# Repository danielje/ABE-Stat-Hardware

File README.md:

# ABE-Stat-Hardware
ABE-Stat Hardware Design / Assembly Files
For Android source code for wireless interface for device, go to https://github.com/danielje/ABE-Stat
For firmware source code (Arduino IDE) go to https://github.com/danielje/ABE-Stat-Arduino

Comprehensive documentation for the project is available in the open-source publication here: http://jes.ecsdl.org/content/166/9/B3056.short This set of files is referred to as "Files S1" in the manuscript above.

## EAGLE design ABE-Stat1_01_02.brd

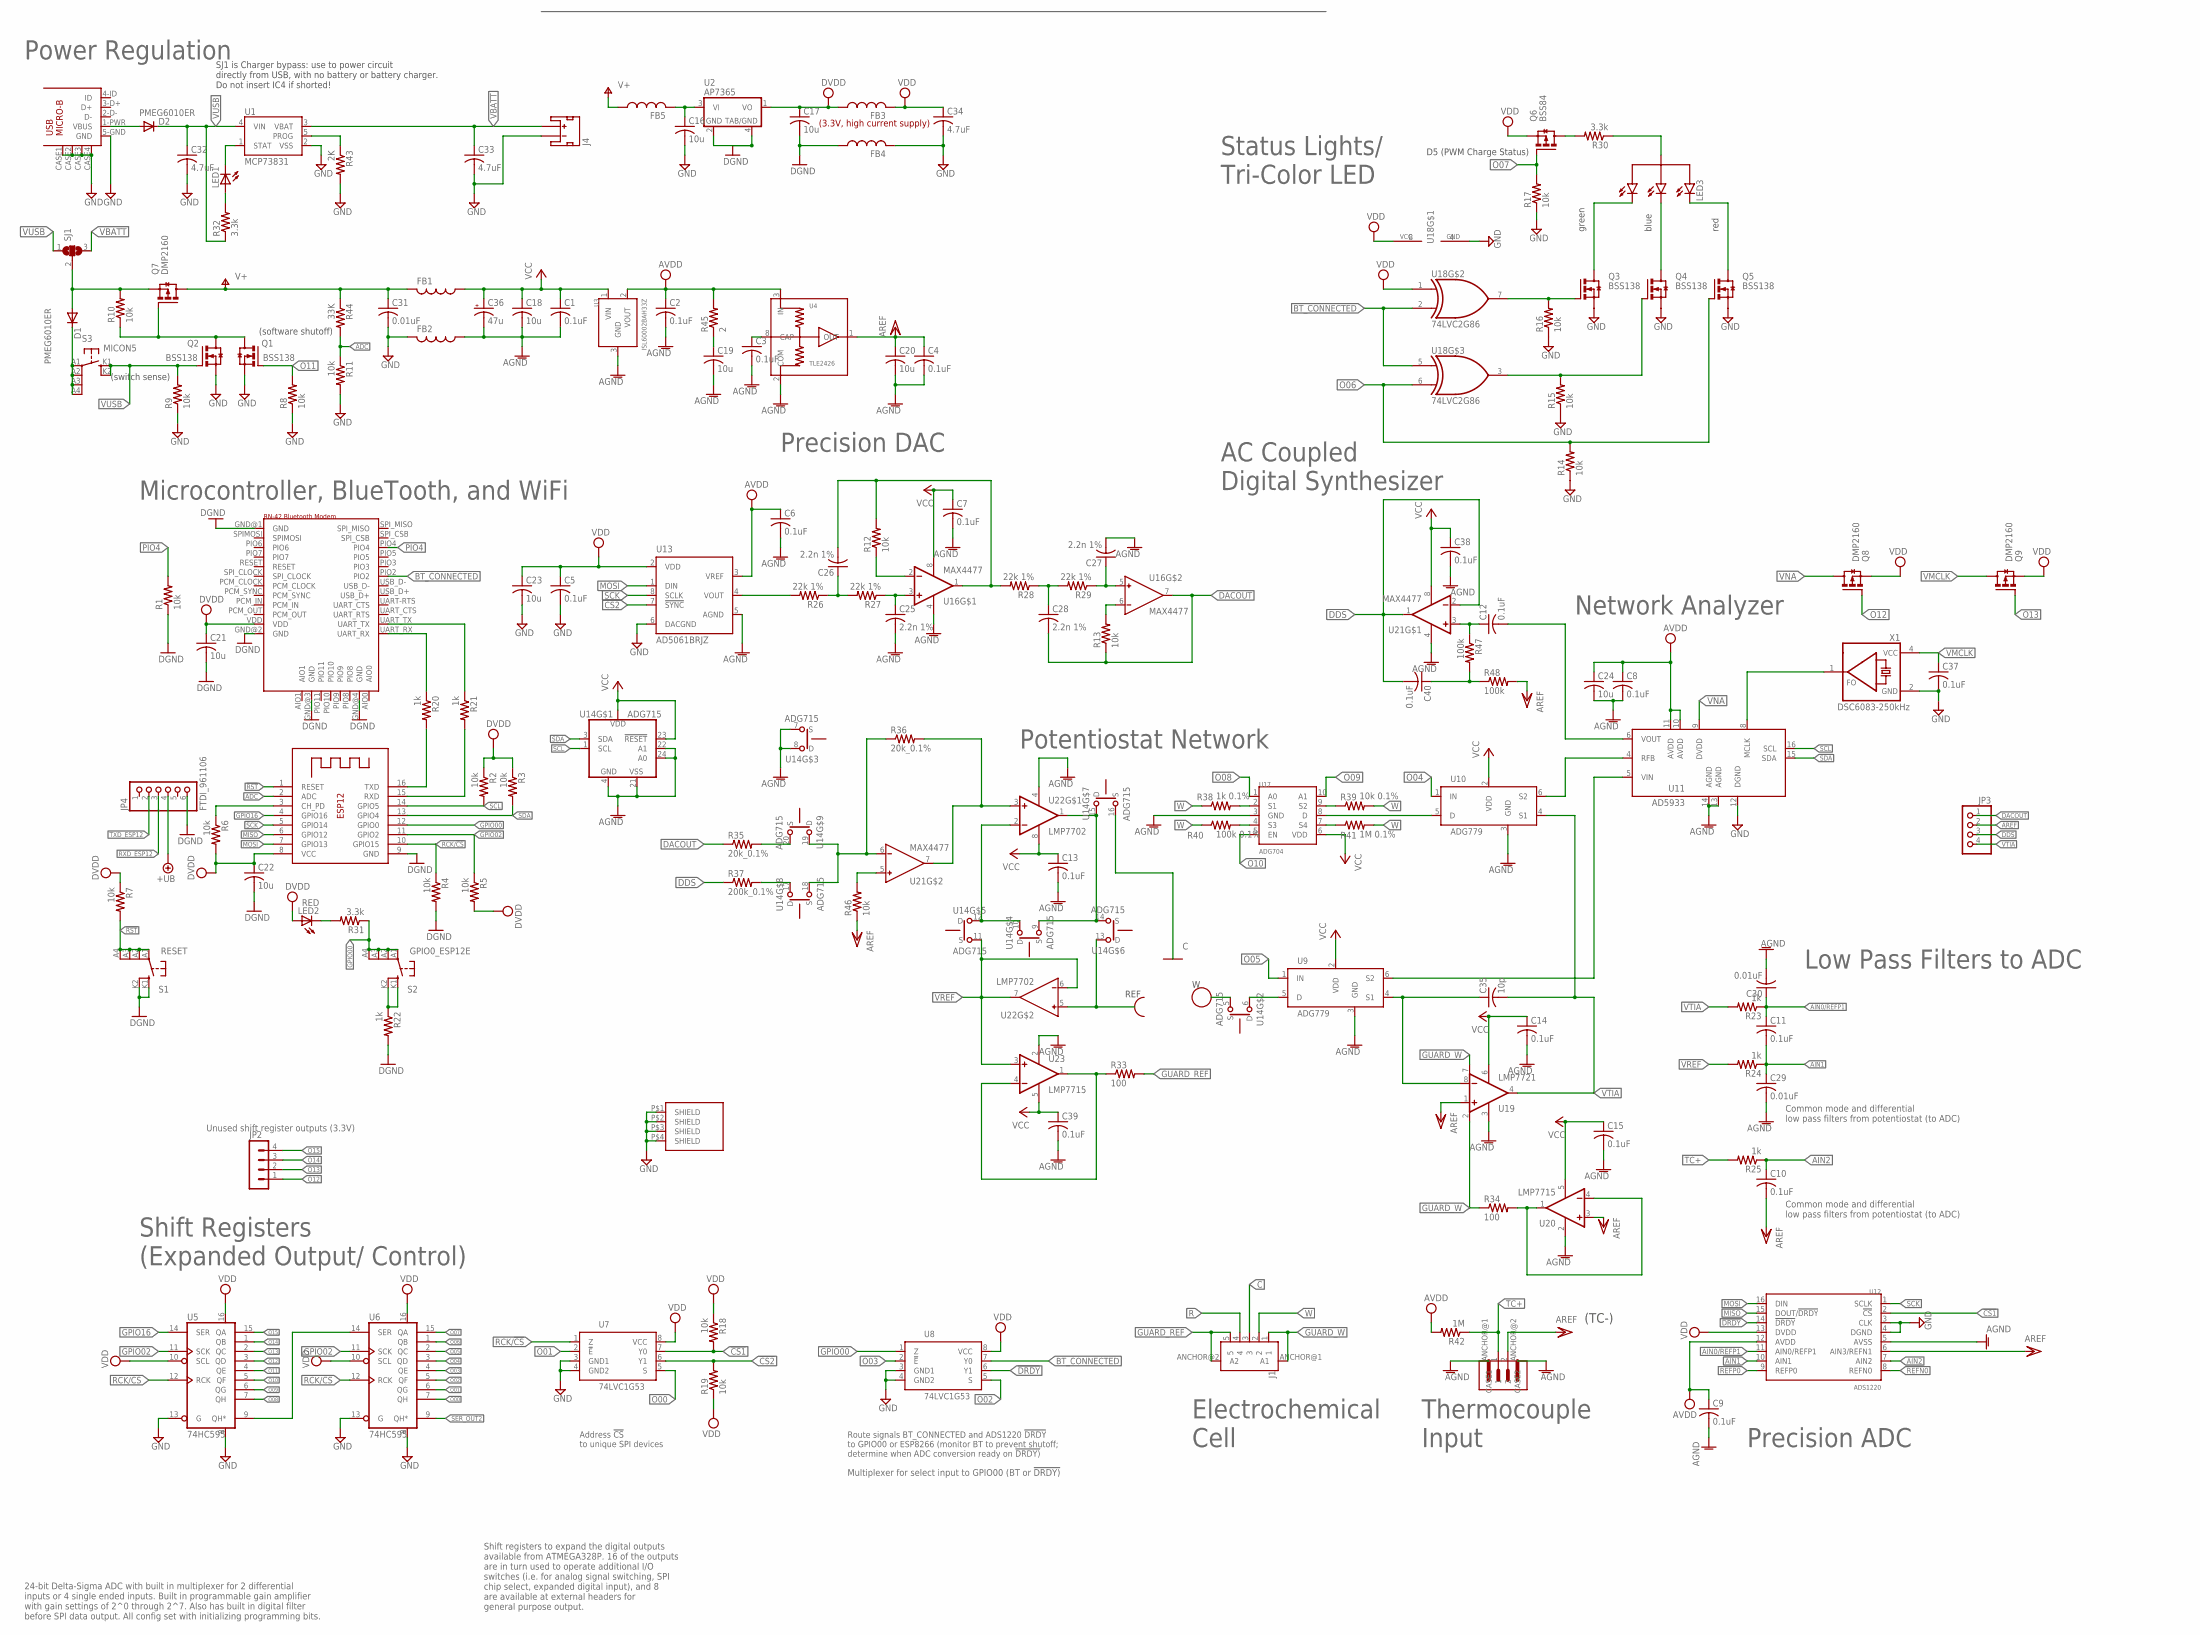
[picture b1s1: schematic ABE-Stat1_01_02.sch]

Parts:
A1: ESP-12E; ESP-12
A2: RN-42_BLUETOOTH; RN-42
C1, C2, C3, C4, C5, C6, C7, C8, C9, C10, C11, C12, C13, C14, C15, C37, C38, C39, C40: 0.1uF; C0805
C16, C17, C18, C19, C20, C21, C22, C23, C24: 10u; C0805
C25, C26, C27, C28: 2.2n 1%; C0805
C29, C30, C31: 0.01uF; C0805
C32, C33, C34: 4.7uF; C0805
C35: 10p; C0805
C36: 47u; D/7343-31W
D1, D2: PMEG6010ER; DIODE_SOD123
FB1, FB2, FB3, FB4, FB5: FERRITE_BEAD_5A_0805; R0805
J1: 5-PIN-VERTICAL-PHOENIX_2.5MM-SMD; 5-PIN-VERT_PHOENIX_SMD
J2: 1A_JENKINS_2013_2PIN_SMD_PHOENIX_CONTACTVERTICAL; 2-PIN-VERT_PHOENIX_SMD
J3: USB-MICRO-B; USB_MICRO_B_WURTH_629105136821
J4: JST_2MM_MALE; JST-2-SMD
JP2: MA04-1
JP3: PINHD-1X4; 1X04
JP4: FTDI_961106; 6_PIN_0.1IN_STRAIGHT_HEADER
LED1: LEDCHIPLED_1206; CHIPLED_1206
LED2: RED; LED-1206
LED3: LED_RBG_COM_ANODE; LED_RGB_WURTH_150141M173100
Q1, Q2, Q3, Q4, Q5: BSS138; SOT-23
Q6: BSS84; SOT-23-3
Q7, Q8, Q9: DMP2160; SOT-23-3
R1, R2, R3, R4, R5, R6, R7, R8, R9, R10, R11, R12, R13, R14, R15, R16, R17, R18, R19, R46: 10k; R0805
R20, R21, R22, R23, R24, R25: 1k; R0805
R26, R27, R28, R29: 22k 1%; R0805
R30, R31, R32: 3.3k; R0805
R33, R34: 100; R0805
R35, R36: 20k_0.1%; R0805
R37: 200k_0.1%; R0805
R38: 1k 0.1%; R0805
R39: 10k 0.1%; R0805
R40: 100k 0.1%; R0805
R41: 1M 0.1%; R0805
R42: 1M; R0805
R43: 2K; R0805
R44: 33K; R0805
R45: 2; R2512
R47, R48: 100k; R0805
S1: RESET; RAFI-MICON5_SWITCH
S2: GPIO0_ESP12E; RAFI-MICON5_SWITCH
S3: MICON5; RAFI-MICON5_SWITCH
SH1: SMARTDART_SHIELD; SMARTDART-SHIELD
SJ1: SJ2W; SJ_2
U1: MCP73831; SOT23-5
U2: AP7365; SOT-223
U3: ISL60002BAH33Z; SOT-23-3
U4: TLE2426; SOIC-8
U5, U6: 74HC595; TSSOP16
U7, U8: 74LVC1G53; VSSOP8
U9, U10: ADG779; SC70-6
U11: AD5933; SSOP-16
U12: ADS1220; TSSOP16
U13: AD5061BRJZ; SOT-23-8
U14: ADG715; TSSOP24
U16, U21: MAX4477; UMAX8
U17: ADG704; MSOP10
U18: 74LVC2G86; US-8
U19: LMP7721; SOIC-8
U20, U23: LMP7715; SOT23-5
U22: LMP7702; MSOP8
X1: DSC6083-250kHz; DSC60XX_OSCILLATOR_3.2X2.5MM

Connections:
!CS1: R18.2, U7.7 (Y0), U12.2 (!CS)
!CS2: R19.2, U7.6 (Y1), U13.7 (!SYNC)
!DRDY: U8.6 (Y1), U12.14 (!DRDY)
!RST: A1.1 (RESET), R7.2, S1.A1, S1.A2 (P1), S1.A3 (P2), S1.A4 (P3)
+UB: JP4.4
AD5933_VIN: U9.6 (S2), U11.5 (VIN)
ADC: A1.2 (ADC), R11.1, R44.2
AGND: C1.2, C2.2, C3.2, C4.2, C6.2, C7.2, C8.2, C9.2, C13.2, C14.2, C15.2, C18.2, C19.2, C20.2, C24.2, C25.2, C27.2, C29.2, C30.2, C36.-, C38.2, C39.2, FB2.1, J2.ANCHOR@1 (CASE1), J2.ANCHOR@2 (CASE2), U3.3 (GND), U4.2 (COM), U9.3 (GND), U10.3 (GND), U11.13 (AGND), U11.14 (AGND), U12.5 (AVSS), U13.5 (AGND), U14.4 (GND), U14.7 (S), U14.8 (D), U14.21 (VSS), U14.22 (A1), U14.24 (A0), U16.4 (V-), U17.3 (GND), U19.3 (V-), U20.2 (V-), U21.4 (V-), U22.4 (V-), U23.2 (V-)
AIN0/REFP1: C11.1, C30.1, R23.1, U12.11 (AIN0/REFP1)
AIN1: C11.2, C29.1, R24.1, U12.10 (AIN1)
AIN2: C10.1, R25.1, U12.7 (AIN2)
AREF: C4.1, C10.2, C20.1, J2.2, JP3.2, R46.1, R48.2, U4.1 (OUT), U12.6 (AIN3/REFN1), U19.1 (+IN), U20.3 (+IN)
AVDD: C2.1, C6.1, C8.1, C9.1, C24.1, R42.2, R45.2, U3.2 (VOUT), U4.3 (IN), U11.10 (AVDD), U11.11 (AVDD), U12.12 (AVDD), U13.3 (VREF)
BT_CONNECTED: A2.PIO2, U8.7 (Y0), U18.2 (I1), U18.5 (I0)
C: J1.3, U14.16 (S)
DACOUT: C28.2, JP3.1, R13.1, R35.1, U16.7 (OUT)
DDS: C40.2, JP3.3, R37.1, U21.1 (OUT), U21.2 (-IN)
DGND: A1.9 (GND), A2.GND@1 (GND), A2.GND@2 (GND), A2.GND@3 (GND), A2.GND@4 (GND), C17.2, C21.2, C22.2, FB4.1, JP4.6, R1.1, R4.2, R22.2, S1.K1 (S), S1.K2 (S1), U2.2 (GND), U2.4 (GND1)
DVDD: A1.8 (VCC), A2.VDD, C17.1, C21.1, C22.1, FB3.1, LED2.A, R2.1, R3.1, R5.2, R6.2, R7.1, U2.1 (VO)
GND: C5.2, C16.2, C23.2, C31.2, C32.2, C33.2, C34.2, C37.2, FB2.2, FB4.2, J3.5-GND (GND), J3.CASE1 (CASE), J3.CASE2 (CASE), J3.CASE3 (CASE), J3.CASE4 (CASE), J4.1 (-), Q1.2-S (S), Q2.2-S (S), Q3.2-S (S), Q4.2-S (S), Q5.2-S (S), R8.1, R9.1, R11.2, R14.1, R15.1, R16.1, R17.1, R43.2, SH1.P$1, SH1.P$2, SH1.P$3, SH1.P$4, U1.2 (VSS), U5.8 (GND), U5.13 (G), U6.8 (GND), U6.13 (G), U7.3 (GND1), U7.4 (GND2), U8.3 (GND1), U8.4 (GND2), U11.12 (DGND), U12.3 (CLK), U12.4 (DGND), U13.6 (DACGND), U18.4 (GND), X1.2 (GND)
GPIO00: A1.12 (GPIO0), R31.1, S2.A1, S2.A2 (P1), S2.A3 (P2), S2.A4 (P3), U8.1 (Z)
GPIO02: A1.11 (GPIO2), R5.1, U5.11 (SCK), U6.11 (SCK)
GPIO16: A1.4 (GPIO16), U5.14 (SER)
GUARD_REF: J1.5, J1.ANCHOR@2 (A2), R33.2
GUARD_W: J1.1, J1.ANCHOR@1 (A1), R34.1, U19.2 (GUARD), U19.7 (GUARD)
MISO: A1.6 (GPIO12), U12.15 (DOUT/!DRDY)
MOSI: A1.7 (GPIO13), U12.16 (DIN), U13.1 (DIN)
unnamed: A2.UART_RX, R20.1
unnamed: U14.10 (D), U14.12 (D), U22.2 (-IN)
unnamed: D2.A, J3.1-PWR (VBUS)
unnamed: A2.UART_TX, R21.1
unnamed: Q3.1-G (G), R16.2, U18.7 (O)
unnamed: U9.5 (D), U14.6 (D)
unnamed: R43.1, U1.5 (PROG)
unnamed: U5.9 (QH*), U6.14 (SER)
unnamed: C25.1, R27.1, U16.3 (+IN)
unnamed: LED1.C, U1.1 (STAT)
unnamed: R26.2, U13.4 (VOUT)
unnamed: LED1.A, R32.2
unnamed: C19.1, R45.1
unnamed: R37.2, U14.17 (D)
unnamed: C26.1, R26.1, R27.2
unnamed: R22.1, S2.K1 (S), S2.K2 (S1)
unnamed: Q4.1-G (G), R15.2, U18.3 (O)
unnamed: D1.C, S3.A1, S3.A2 (P1), S3.A3 (P2), S3.A4 (P3)
unnamed: C3.1, U4.8 (CAP)
unnamed: C26.2, R12.2, R28.2, U16.1 (OUT)
unnamed: C28.1, R28.1, R29.2
unnamed: C27.1, R29.1, U16.5 (IN+)
unnamed: R12.1, U16.2 (-IN)
unnamed: U14.9 (S), U14.14 (S), U14.15 (D), U22.1 (OUT)
unnamed: R13.2, U16.6 (IN-)
unnamed: LED2.C, R31.2
unnamed: C35.1, U9.4 (S1), U19.8 (-IN)
unnamed: R36.1, U14.18 (S), U14.19 (D), U21.6 (IN-)
unnamed: R36.2, U21.7 (OUT), U22.3 (+IN)
unnamed: U10.6 (S2), U11.4 (RFB)
unnamed: R41.1, U17.7 (S4)
unnamed: R33.1, U23.1 (OUT), U23.4 (-IN)
unnamed: R39.1, U17.9 (S2)
unnamed: Q1.3-D (D), Q2.3-D (D), Q7.1 (G), R10.1
unnamed: U10.5 (D), U17.8 (D)
unnamed: R38.2, U17.2 (S1)
unnamed: R40.2, U17.4 (S3)
unnamed: LED3.G, Q3.3-D (D)
unnamed: R34.2, U20.1 (OUT), U20.4 (-IN)
unnamed: LED3.B, Q4.3-D (D)
unnamed: LED3.R, Q5.3-D (D)
unnamed: Q6.3 (D), R30.2
unnamed: LED3.A, R30.1
unnamed: R35.2, U14.20 (S)
unnamed: C16.1, FB5.2, U2.3 (VI)
unnamed: A1.3 (CH_PD), R6.1
unnamed: U11.8 (MCLK), X1.1 (FO)
unnamed: D1.A, Q7.2 (S), R10.2, SJ1.2
unnamed: R46.2, U21.5 (IN+)
unnamed: C40.1, R47.2, R48.1
unnamed: C12.1, R47.1, U21.3 (+IN)
unnamed: C12.2, U11.6 (VOUT)
O00: U6.7 (QH), U7.5 (S)
O01: U6.6 (QG), U7.2 (!E)
O02: U6.5 (QF), U8.5 (S)
O03: U6.4 (QE), U8.2 (!E)
O04: U6.3 (QD), U10.1 (IN)
O05: U6.2 (QC), U9.1 (IN)
O06: Q5.1-G (G), R14.2, U6.1 (QB), U18.6 (I1)
O07: Q6.1 (G), R17.2, U6.15 (QA)
O08: U5.7 (QH), U17.1 (A0)
O09: U5.6 (QG), U17.10 (A1)
O10: U5.5 (QF), U17.5 (EN)
O11: Q1.1-G (G), R8.2, U5.4 (QE)
O12: JP2.1, Q8.1 (G), U5.3 (QD)
O13: JP2.2, Q9.1 (G), U5.2 (QC)
O14: JP2.3, U5.1 (QB)
O15: JP2.4, U5.15 (QA)
PIO4: A2.PIO4, R1.2
R: J1.4, U14.13 (D), U22.5 (IN+)
RCK/!CS: A1.10 (GPIO15), R4.1, U5.12 (RCK), U6.12 (RCK), U7.1 (Z)
REFN0: U12.8 (REFN0)
REFP0: U12.9 (REFP0)
RXD_ESP12: A1.15 (RXD), JP4.3, R21.2
SCK: A1.5 (GPIO14), U12.1 (SCLK), U13.8 (SCLK)
SCL: A1.14 (GPIO5), R2.2, U11.16 (SCL), U14.1 (SCL)
SDA: A1.13 (GPIO4), R3.2, U11.15 (SDA), U14.3 (SDA)
SER_OUT2: U6.9 (QH*)
TC+: J2.1, R25.2, R42.1
TXD_ESP12: A1.16 (TXD), JP4.2, R20.2
V+: C31.1, FB1.2, FB5.1, Q7.3 (D), R44.1
VBATT: C33.1, J4.2 (+), SJ1.3, U1.3 (VBAT)
VCC: C1.1, C7.1, C13.1, C14.1, C15.1, C18.1, C36.+, C38.1, C39.1, FB1.1, U3.1 (VIN), U9.2 (VDD), U10.2 (VDD), U14.2 (VDD), U14.23 (!RESET), U16.8 (V+), U17.6 (VDD), U19.6 (V+), U20.5 (V+), U21.8 (V+), U22.8 (V+), U23.5 (V+)
VDD: C5.1, C23.1, C34.1, FB3.2, Q6.2 (S), Q8.2 (S), Q9.2 (S), R18.1, R19.1, U5.10 (SCL), U5.16 (VCC), U6.10 (SCL), U6.16 (VCC), U7.8 (VCC), U8.8 (VCC), U12.13 (DVDD), U13.2 (VDD), U18.1 (I0), U18.8 (VCC)
VMCLK: C37.1, Q9.3 (D), X1.4 (VCC)
VNA: Q8.3 (D), U11.9 (DVDD)
VREF: R24.2, U14.11 (S), U22.6 (IN-), U22.7 (OUT), U23.3 (+IN)
VTIA: C35.2, JP3.4, R23.2, U10.4 (S1), U19.4 (OUT)
VUSB: C32.1, D2.C, Q2.1-G (G), R9.2, R32.1, S3.K1 (S), S3.K2 (S1), SJ1.1, U1.4 (VIN)
W: J1.2, R38.1, R39.2, R40.1, R41.2, U14.5 (S)

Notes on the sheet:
(3.3V, high current supply)
Route signals BT_CONNECTED and ADS1220 !DRDY to GPIO00 or ESP8266 (monitor BT to prevent shutoff; determine when ADC conversion ready on !DRDY)
Shift registers to expand the digital outputs available from ATMEGA328P. 16 of the outputs are in turn used to operate additional I/O switches (i.e. for analog signal switching, SPI chip select, expanded digital input), and 8 are available at external headers for general purpose output.
Multiplexer for select input to GPIO00 (BT or !DRDY)
Power Regulation
Microcontroller, BlueTooth, and WiFi
Precision ADC
Shift Registers (Expanded Output/ Control)
24-bit Delta-Sigma ADC with built in multiplexer for 2 differential inputs or 4 single ended inputs. Built in programmable gain amplifier with gain settings of 2^0 through 2^7. Also has built in digital filter before SPI data output. All config set with initializing programming bits.
Common mode and differential low pass filters from potentiostat (to ADC)
Address !CS to unique SPI devices
(switch sense)
(software shutoff)
Precision DAC
Network Analyzer
Potentiostat Network
Low Pass Filters to ADC
Thermocouple Input
Electrochemical Cell
D5 (PWM Charge Status)
green
blue
red
Status Lights/ Tri-Color LED
(TC-)
Unused shift register outputs (3.3V)
REF
SJ1 is Charger bypass: use to power circuit directly from USB, with no battery or battery charger. Do not insert IC4 if shorted!
AC Coupled Digital Synthesizer

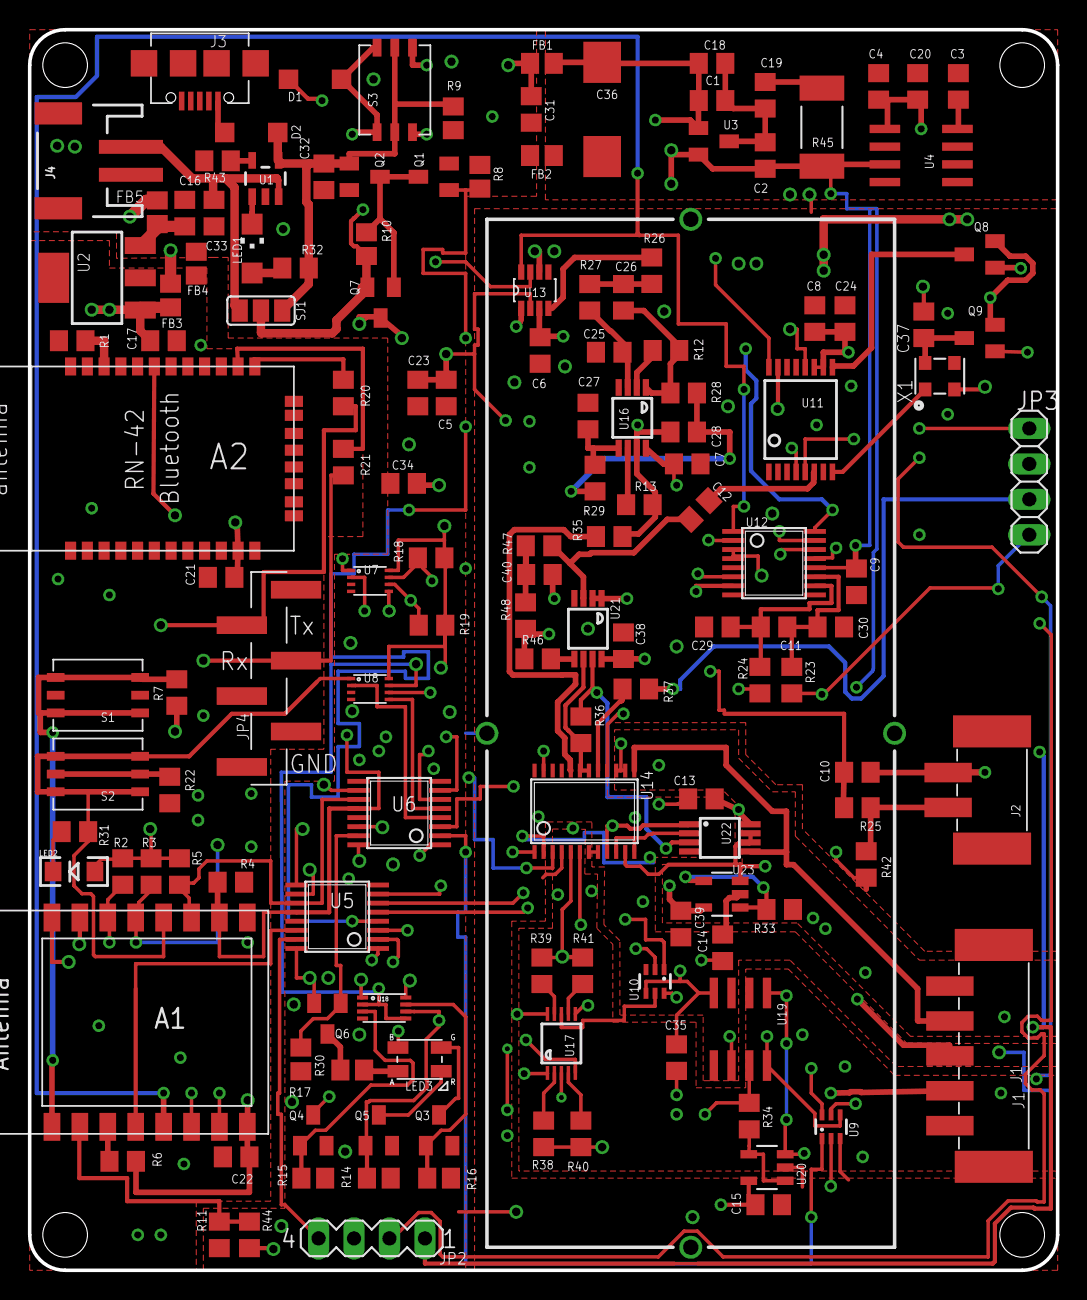
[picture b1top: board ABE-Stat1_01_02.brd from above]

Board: 4 copper layers, 73.7 x 88.9 mm, 144 parts (0 on the bottom side), 113 nets.

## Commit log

2018-11-16 ABE-Stat Hardware Files
    EAGLE schematic and layout, + gerber, BOM, and centroid files for fabrication and assembly

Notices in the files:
parts and their libraries:
SparkFun-Connectors: Licensing: Creative Commons ShareAlike 4.0 International - https://creativecommons.org/licenses/by-sa/4.0
